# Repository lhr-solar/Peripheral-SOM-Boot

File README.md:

# Peripheral SOM Daughterboard
Template with aligned M3 holes and board to board connector placement.

# How to Use
- Repositories -> New repository -> Repository template
- Naming convention: (System Name)-Peripheral-SOM-Daughterboard-(Function)

# Specifications
- SPI1 is main SPI
- I2C1 is main I2C
- SPI2 can be swapped out for 4xGPIO
- I2C2 can be swapped out for 2xGPIO
- 3.3V Power
- 3.3V Analog
- 5V Power (Unisolated)
- Associated Grounds

# Design Considerations
- Can be larger than Peripheral SOM
- Front layer (top) will be sandwiched with Peripheral SOM
  - **Throughole and other bottom mounted Peripheral SOM components may interfere with front layer (top)**
  - Outline provided on drawing layer for convenience

# Images

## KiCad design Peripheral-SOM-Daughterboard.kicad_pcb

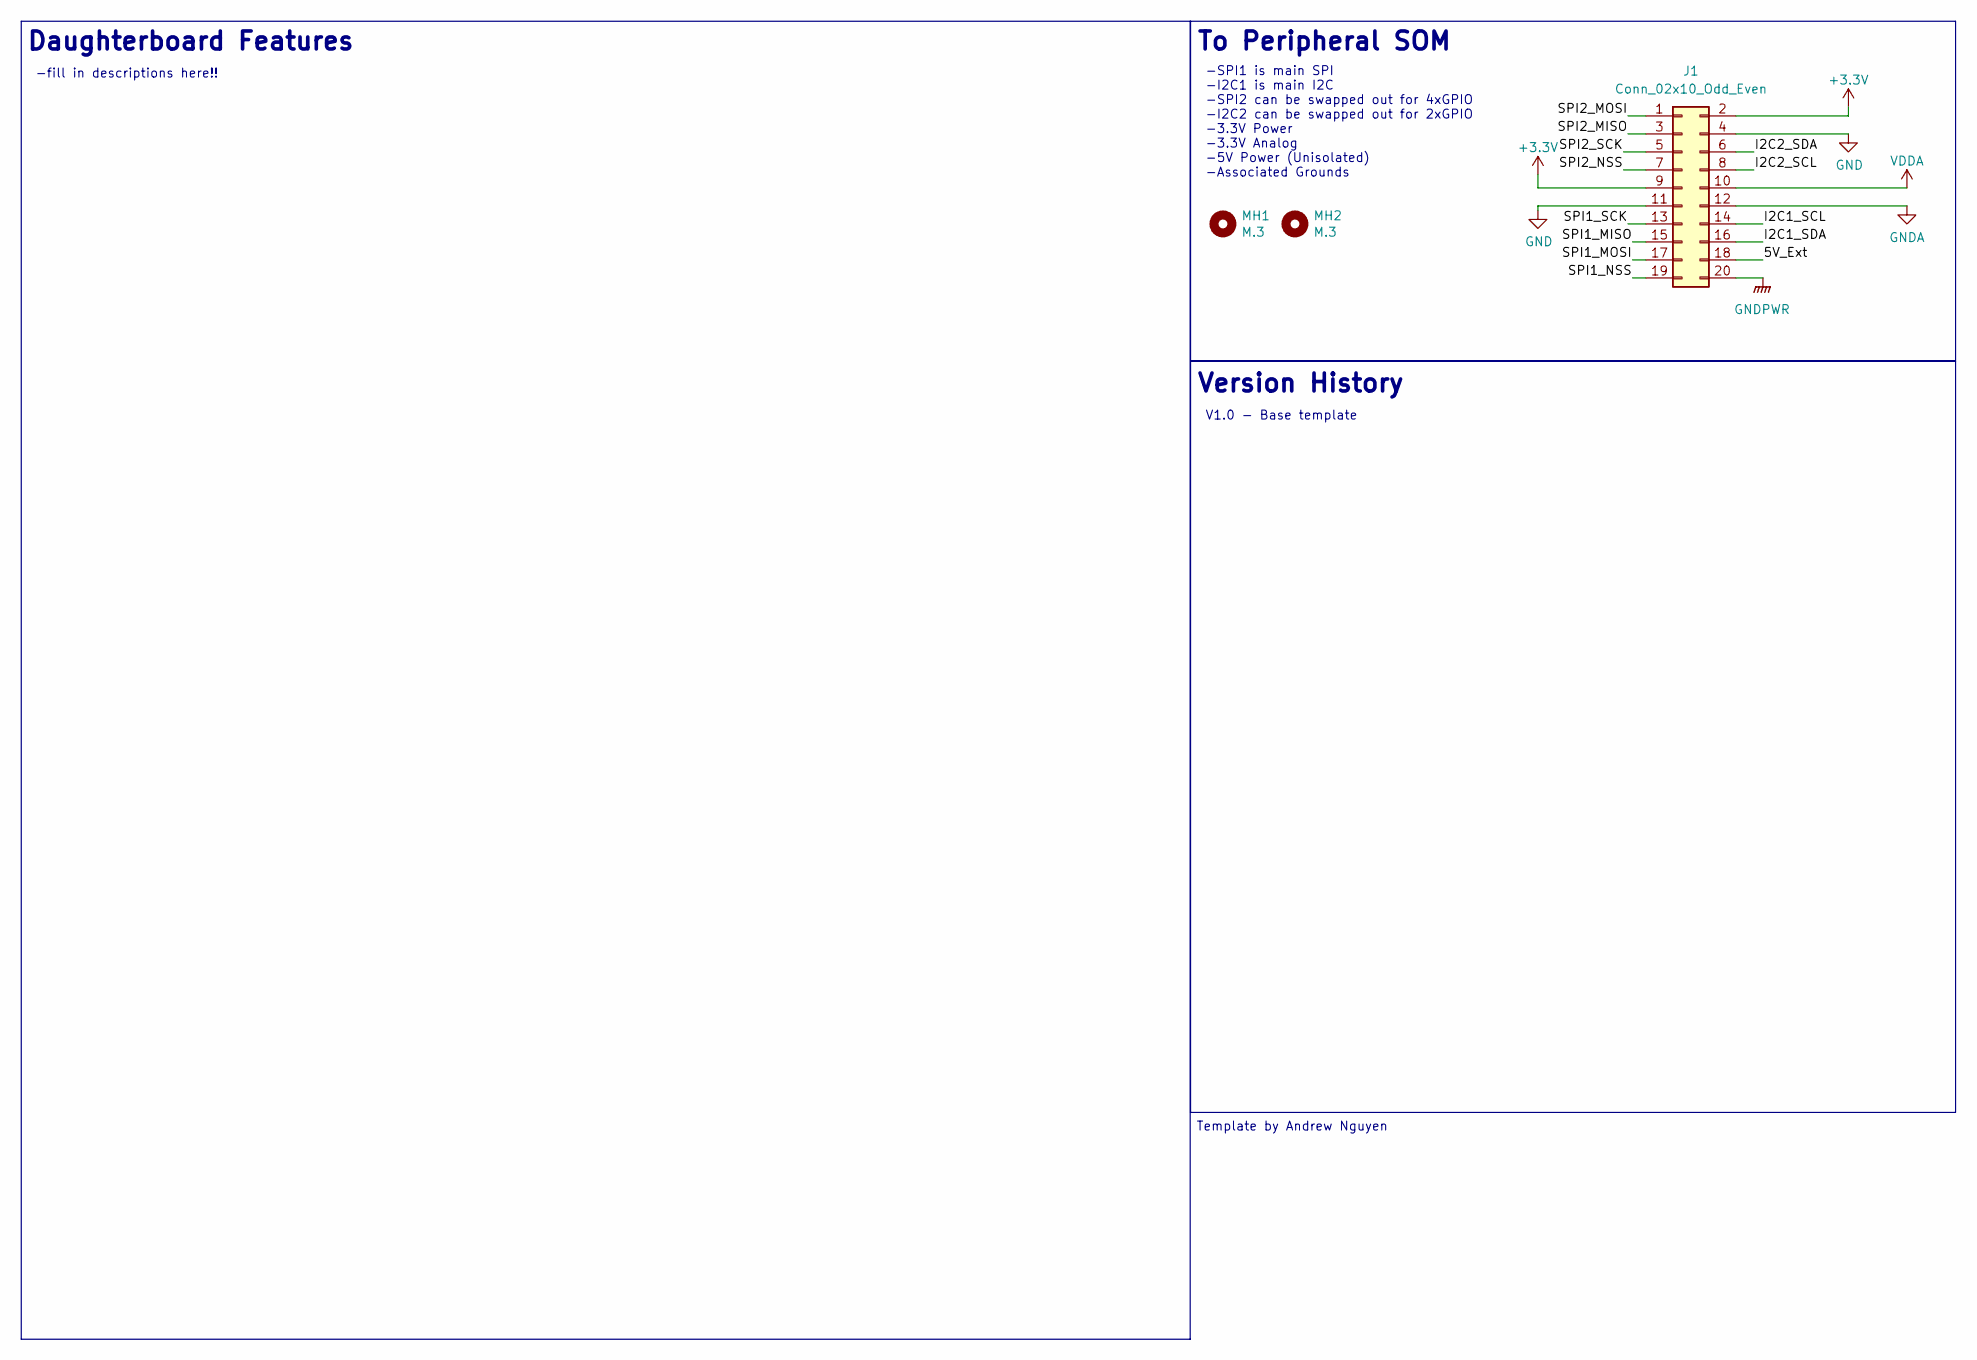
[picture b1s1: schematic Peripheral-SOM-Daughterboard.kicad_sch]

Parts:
J1: Conn_02x10_Odd_Even; Molex_53307-2071
MH1, MH2: M.3; MountingHole_3mm

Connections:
+3.3V: J1.2, J1.9
/5V_Ext: J1.18
/I2C1_SCL: J1.14
/I2C1_SDA: J1.16
/I2C2_SCL: J1.8
/I2C2_SDA: J1.6
/SPI1_MISO: J1.15
/SPI1_MOSI: J1.17
/SPI1_NSS: J1.19
/SPI1_SCK: J1.13
/SPI2_MISO: J1.3
/SPI2_MOSI: J1.1
/SPI2_NSS: J1.7
/SPI2_SCK: J1.5
GND: J1.4, J1.11
GNDA: J1.12
GNDPWR: J1.20
VDDA: J1.10

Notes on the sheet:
To Peripheral SOM
-fill in descriptions here!!
Template by Andrew Nguyen
Daughterboard Features
-SPI1 is main SPI -I2C1 is main I2C -SPI2 can be swapped out for 4xGPIO -I2C2 can be swapped out for 2xGPIO -3.3V Power -3.3V Analog -5V Power (Unisolated) -Associated Grounds
V1.0 - Base template
Version History

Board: 2 copper layers, 3 parts (0 on the bottom side), 2 nets, no tracks yet.

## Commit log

2023-08-26 initial boot template
2023-08-26 naming
2023-08-26 more naming...
2023-08-26 relative library paths
2023-08-28 added dimensions
2023-08-28 Update README.md pcb image
2023-09-20 Updated template for new SOM pinout + added lck and backups to gitignore
